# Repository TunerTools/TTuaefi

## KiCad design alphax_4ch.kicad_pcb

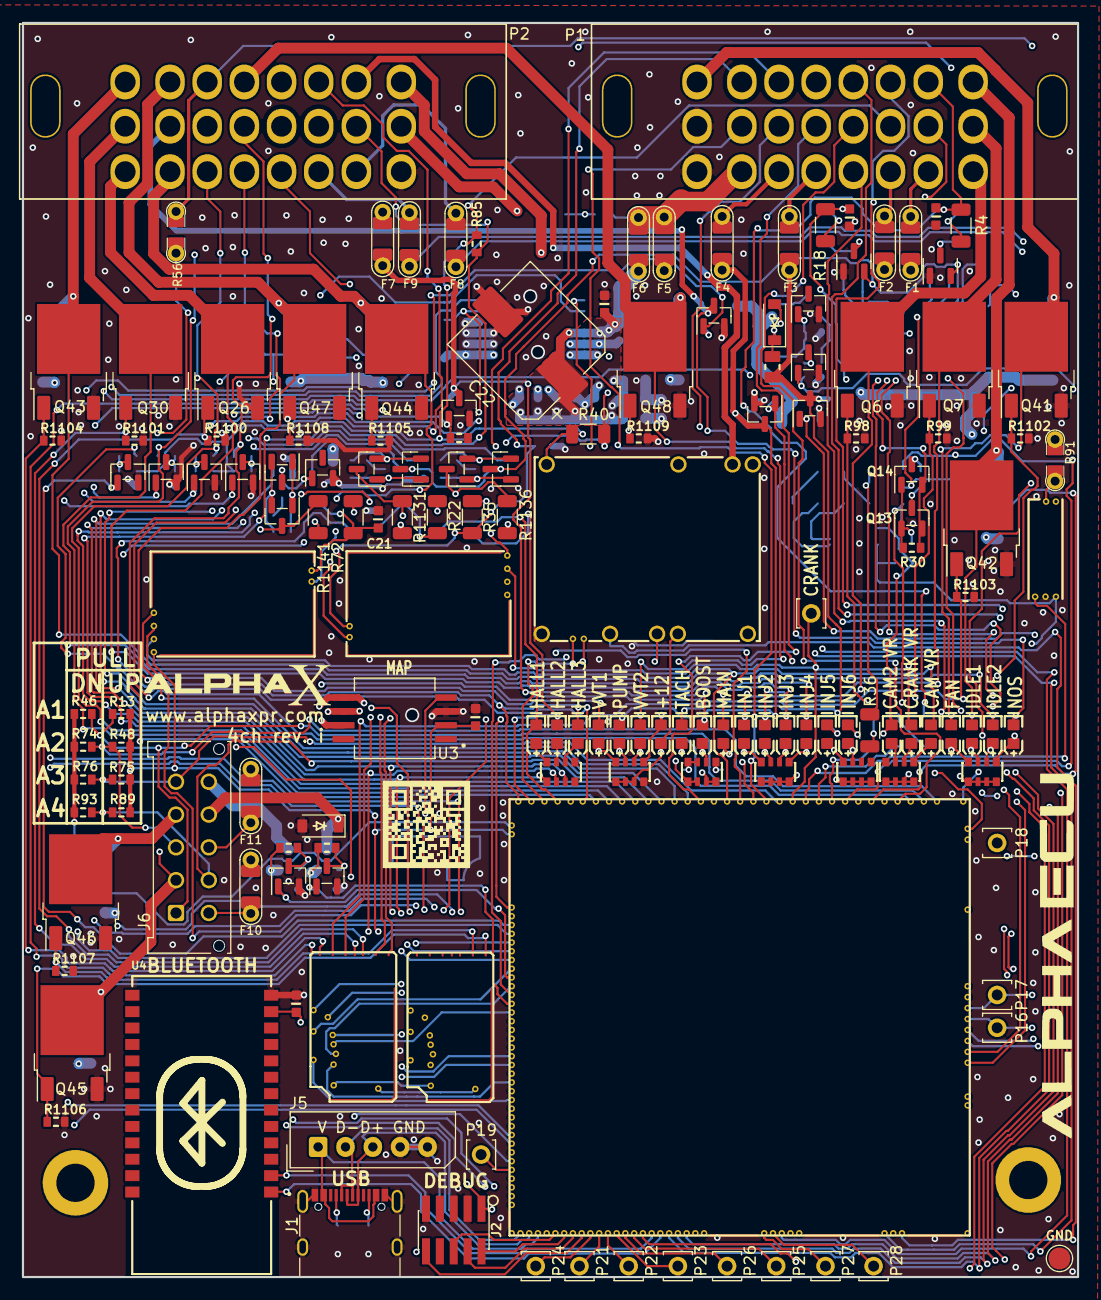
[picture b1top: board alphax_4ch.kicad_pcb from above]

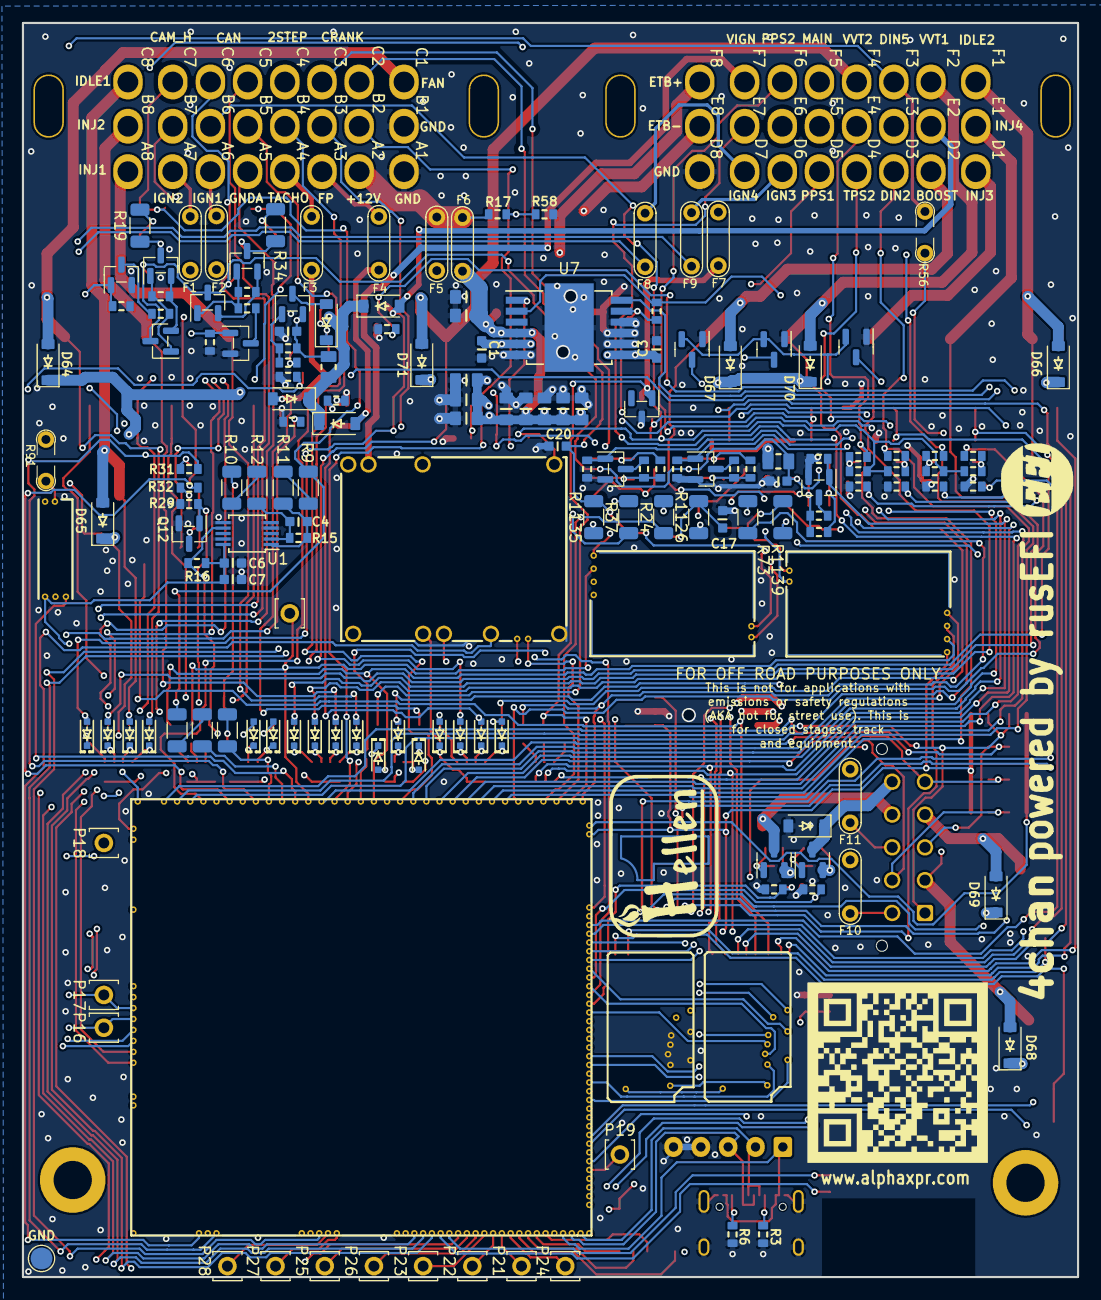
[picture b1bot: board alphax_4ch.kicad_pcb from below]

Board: 4 copper layers, 96.5 x 114.7 mm, 291 parts (134 on the bottom side), 230 nets.

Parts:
C1, C3: 10n; C0603
C2, C5, C6, C18, C19, C55: 100n; C0603
C4: 1n; C0603
C7: 22u; C0603
C8, C9, C17, C20, C21: 1n 250V; C0603
C22: 470uF; CP_Elec_10x10.5
C45, C46, C47, C48, C49, C50, C51, C52, C53, C54: 10u; C0805
D1, D2, D3, D5, D6, D7, D8, D21, D22, D24, D37, D38, D41, D42, D45, D46, D53: 1N4148WS; SOD-323
D4, D10, D33, D34, D35, D36: LED-WHITE-0603; LED-0603
D9, D13, D14, D15, D16, D17, D31, D32, D39, D40, D43, D44, D47, D48, D56, D57: LED-RED-0603; LED-0603
D18, D19, D23, D55, D58: BAT54S; SOT-23
D20: LED-GREEN-0603; LED-0603
D25, D28, D29: PSM712-LF; SOT-23
D26, D27, D49, D50, D51, D52, D64, D65, D66, D67, D68, D69, D70, D71, D72: B5819W; SOD-123
F1, F2, F8, F9, F10, F11: nSMD005; PAD-1206-PAD
F3, F4, F7: nSMD050; PAD-1206-PAD
F5, F6: 12H1500D; PAD-1206-PAD
G1: RUSEFI_LOGO; rusefi_logo
G3: LOGO
G4: LOGO_AlphaECU; alphax_logo_AlphaECU
G5: LOGO_AlphaX; alphax_logo_AlphaX
G6: ALPHAX_QR_CODE; alphax_qr_code
G7: Disclaimer; Off_Road_Disclaimer
J1: USB_C_Receptacle_USB2.0; USB_C_Receptacle_XKB_U262-16XN-4BVC11
J2: Cortex_Debug; PinHeader_2x05_P1.27mm_Vertical_SMD
J3, J4: Conn_01x01; TestPoint_Pad_D2.0mm
J5: Conn_01x05_Male; Molex_SPOX_5267-05A_1x05_P2.50mm_Vertical
J6: 430451012; Molex_Micro-Fit_3.0_43045-1012_2x05_P3.00mm_Vertical
J7, J8: Conn_01x01; MountingHole_4.5mm_Pad
M1: Module-power_12and5V-0.2; power_12and5V
M2, M6: Module-ign8-0.2; ign8
M3, M8: Module-vr-discrete-0.4; vr-discrete
M4: Module-mega-mcu144-0.5; mega-mcu144
M9: Module-knock-0.2; knock
P1: HCCPHPE24BKA90F; 33311-24AW-2
P2: HCCPHPE24BGYB90F; 33311-24AW-2
P4, P16, P17, P18, P19, P21, P22, P23, P24, P25, P26, P27, P28: Pad; PAD-TH
Q1, Q3, Q4, Q8, Q9, Q10, Q11, Q12, Q17, Q20, Q22, Q23, Q24, Q27, Q29, Q31, Q51: AO3400A; SOT-23
Q2, Q16: PJM2319PSA; SOT-23
Q6, Q7, Q26, Q30, Q41, Q42, Q43, Q44, Q45, Q46, Q47, Q48: VND14NV04-E; DPAK
Q13, Q14, Q18, Q19, Q21, Q25, Q28, Q35, Q36, Q49, Q50, Q52, Q53: AO3401A; SOT-23
R1, R2, R5, R26, R50, R51: 4.7k; R0603-4
R3, R6: 5.6k; R0603
R4, R18, R19, R34, R1126, R1131, R1135, R1136, R1139, R1141: 2k; R_1206_3216Metric
R7, R8, R14, R20, R27, R29, R30, R38, R39, R41, R42, R43, R44, R52, R53, R54, R55, R57, R86, R87, R88, R98, R99, R1100, R1101, R1102, R1103, R1104, R1105, R1106, R1107, R1108, R1109, R1110, R1111, R1112, R1113, R1125, R1127, R1128, R1129, R1132, R1137, R1138, R1140: 4.7k; R0603
R9, R10, R11, R12, R21, R22, R23, R24, R35, R36, R37, R47, R72, R73: 4.7k; R_1206_3216Metric
R13, R15, R48, R75, R89: R0603
R16: 10k; R0603
R17: 33k; R0603
R25: 470; R0805
R28, R78, R79, R80: 1.2k; R0603
R31, R32: 2.7k; R0603
R33: 220; R0805
R40: SMD1206B035TF/16; R_1206_3216Metric
R45: 750; R0805
R46, R74, R76, R93: 680k; R0603
R49: 1k; R0603-4
R56, R91: Jumper-Pad-Pad; PAD-0805-PAD
R58: 6.8k; R0603
R81, R82, R83, R84, R85: 3.3k; R0603
U1: MAX9924UAUB+; MSOP-10_3x3mm_P0.5mm
U3: MPXH6400A; MPXH6400A-SSOP8
U4: JDY-33
U7: TLE9201SG; Infineon_PG-DSO-12-11

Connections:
+3.3V: J2.1, M4.N22 (V33), R8.2, U7.2 (VSO)
+3.3VA: C19.2, M2.V10 (V33), M4.N28 (V33_SWITCHABLE), M6.V10 (V33), U4.12 (3V3)
+5V: M1.E4 (V5), M4.N31 (VCC)
+5VA: C2.2, C6.2, C7.2, D27.2 (A), M2.V9 (VCC), M3.E4 (V5_IN), M4.E38 (V5A_SWITCHABLE), M4.W2 (V5A_SWITCHABLE), M6.V9 (VCC), M8.E4 (V5_IN), M9.E1 (V5A), R1.1, R1.2, R1.3, R1.4, R13.2, R16.2, R40.1, R48.2, R50.1, R50.2, R75.2, R89.2, U1.10 (VCC), U3.2 (Vs)
+5VAS: M1.V4 (5VP), P1.14 (B6), Q13.3 (S), Q14.3 (S), R28.2, R30.2, R40.2, R78.2, R79.2, R80.2, R85.2
+12V: D20.1 (A), D22.1 (K), M1.E2 (V12), R2.1, R2.2, R2.3, R2.4, R5.1, R5.2, R5.3, R26.1, R26.2, R26.3, R26.4, R50.3, R50.4, R51.1, R51.2, R51.3, R51.4
+12V_ETB: C22.1, C45.2, C46.2, C47.2, C48.2, C49.2, C50.2, C51.2, C52.2, C53.2, C54.2, C55.2, F6.2, U7.4 (VS)
+12V_RAW: D49.1 (K), D52.1 (K), D64.1 (K), D65.1 (K), D66.1 (K), D67.1 (K), D68.1 (K), D69.1 (K), D70.1 (K), D71.1 (K), D72.1 (K), F5.2, M1.V1 (V12_PERM), M1.V3 (V12_RAW), Q2.2 (S), Q16.2 (S), R7.2, R20.2, R25.2, R33.2
/2STEP_PULLUP: M4.E23 (OUT_IO7), Q31.1 (G), R57.1
/A2: F5.1, F6.1, P1.2 (A2), R17.1
/A3: F4.1, P1.3 (A3)
/A4: F3.1, P1.4 (A4)
/A6: F2.1, P1.6 (A6)
/A7: F1.1, P1.7 (A7)
/AIN1: J6.1, M4.S32 (IN_TPS2), R13.1, R46.2
/AIN2: J6.3, M4.S33 (IN_PPS2), R48.1, R74.2
/AIN3: J6.5, M4.S21 (IN_MAP1), R75.1, R76.2
/AIN4: J6.7, M4.S11 (IN_AUX3), R89.1, R93.2
/BOOST: M2.S1 (OUT_IGN8), Q44.1 (IN), R1105.1
/CAM2_VR: D4.2 (K), M4.E36 (IO7), R16.1, U1.7 (COUT)
/CAM_PULLUP: M4.N20 (IO4), Q29.1 (G), R55.2
/CAM_VR_PULLUP: M4.E11 (OUT_IO9), Q51.1 (G), R49.3, R1137.1
/CAN+: M4.W12 (CANH), P1.21 (C5)
/CAN-: M4.W13 (CANL), P1.22 (C6)
/CRANK_N_PULLUP: M4.E7 (OUT_IO5), Q1.1 (G), R41.2, R49.2
/CRANK_P_PULLUP: M4.E12 (OUT_IO2), Q3.1 (G), R49.1, R1125.2
/D2_PULLDOWN: M4.E20 (OUT_IO13), Q8.1 (G), R88.1
/D3_PULLDOWN: M4.E22 (OUT_IO8), Q9.1 (G), R87.1
/D4_PULLDOWN: M4.E33 (OUT_INJ7), Q22.1 (G), R86.1
/D5_PULLDOWN: M4.E34 (OUT_INJ8), Q23.1 (G), R27.1
/D6: F9.1, P2.6 (D6)
/D7: F8.1, P2.7 (D7)
/ETB_DIR: M4.N16 (IO1), U7.1 (DIR)
/ETB_DIS: M4.N19 (IO2), R8.1, U7.11 (DIS)
/ETB_PWM: M4.E17 (OUT_PWM2), U7.12 (PWM)
/F3: P2.19 (F3), R56.2, R91.2
/F5: F7.1, P2.21 (F5)
/FAN_RELAY: M2.S4 (OUT_IGN5), Q41.1 (IN), R1102.1
/HALL1: D34.2 (K), M4.S4 (IN_D1), R24.1
/HALL2: D35.2 (K), M4.S2 (IN_D3), R37.1
/HALL3: D36.2 (K), M4.S1 (IN_D4), R73.1
/HALL_OPT_PU/+12V_LIM: C18.2, D18.2 (K), D19.2 (K), D23.2 (K), D28.1, D55.2 (K), D58.2 (K), Q18.2 (D), Q25.2 (D), Q35.2 (D), Q49.2 (D), Q52.2 (D), R25.1
/HS/IN1: M4.E25 (OUT_PWM7), Q4.1 (G), R14.1
/HS/IN2: M4.E28 (OUT_PWM8), Q17.1 (G), R38.1
/IDLE1: M2.S3 (OUT_IGN6), Q42.1 (IN), R1103.1
/IDLE2: M2.S2 (OUT_IGN7), Q43.1 (IN), R1104.1
/INJ1: M2.S8 (OUT_IGN1), Q6.1 (IN), R98.1
/INJ2: M2.S7 (OUT_IGN2), Q7.1 (IN), R99.1
/INJ3: M2.S6 (OUT_IGN3), Q26.1 (IN), R1100.1
/INJ4: M2.S5 (OUT_IGN4), Q30.1 (IN), R1101.1
/INJ5: M6.S8 (OUT_IGN1), Q45.1 (IN), R1106.1
/INJ6: M6.S7 (OUT_IGN2), Q46.1 (IN), R1107.1
/IN_2STEP: M4.S25 (IN_VSS), R47.1
/IN_2STEP_CAM2_VR-: C8.2, P1.20 (C4), R10.2, R18.2, R36.2
/IN_AFR: M4.S15 (IN_O2S2), P1.12 (B4)
/IN_CAM_HALL: M4.S24 (IN_CAM), R23.1
/IN_CAM_HALL_CAM2_VR+: C9.2, P1.23 (C7), R4.2, R9.2, R21.2
/IN_CAM_VR: D33.2 (K), M3.E3 (OUT), M4.S17 (IN_RES1)
/IN_CAM_VR+: C21.2, M3.W2 (VR+), P2.14 (E6), R72.2, R1139.2
/IN_CAM_VR-: M3.W1 (VR-), P2.13 (E5)
/IN_CLT: M4.S28 (IN_CLT), P1.15 (B7), R32.2
/IN_CRANK: D10.2 (K), M4.S22 (IN_CRANK), M8.E3 (OUT), P4.1
/IN_CRANK+: C17.2, M8.W2 (VR+), P1.19 (C3), R22.2, R1126.2
/IN_CRANK-: C20.2, M8.W1 (VR-), P1.18 (C2), R35.2, R1135.2
/IN_D2: M4.S9 (IN_SENS1), P2.3 (D3), R81.1
/IN_D3: M4.S8 (IN_SENS2), P2.11 (E3), R82.1
/IN_D4: M4.S7 (IN_SENS3), P2.12 (E4), R83.1
/IN_D5: M4.S6 (IN_SENS4), R56.1, R84.1
/IN_FLEX: M4.S10 (IN_AUX4), P2.15 (E7), R85.1
/IN_IAT: M4.S26 (IN_IAT), P1.11 (B3), R31.2
/IN_KNOCK: M4.S23 (IN_KNOCK), M9.E3 (OUT_KNOCK)
/IN_KNOCK_RAW: M9.W1 (IN_KNOCK), R91.1
/IN_MAP: M4.S20 (IN_MAP2), P1.10 (B2)
/IN_MAP2: M4.S19 (IN_MAP3), U3.4 (Vout)
/IN_PPS1: M4.S31 (IN_PPS), P2.5 (D5)
/IN_PPS2: M4.S12 (IN_AUX2), P2.22 (F6)
/IN_TPS1: M4.S30 (IN_TPS), P1.13 (B5)
/IN_TPS2: M4.S13 (IN_AUX1), P2.4 (D4)
/IN_VIGN: M1.V2 (IN_VIGN), P2.23 (F7)
/IN_VMAIN: M4.S27 (IN_AT1), R17.2, R58.2
/MAIN: M4.E10 (OUT_IO10), Q10.1 (G), R1113.1
/MCU/NRESET: J2.10, M4.N9 (nReset)
/MCU/SWCLK: J2.4, M4.N8 (SWCLK)
/MCU/SWDIO: J2.2, M4.N7 (SWDIO)
/MCU/SWO: J2.6, M4.N6 (SWO)
/MCU/UART_RX: M4.N18 (UART2_RX), U4.1 (TXD)
/MCU/UART_TX: M4.N17 (UART2_TX), U4.2 (RXD)
/MCU/USB+: J1.A6 (D+), J1.B6 (D+), J5.3, M4.N3 (USBP)
/MCU/USB-: J1.A7 (D-), J1.B7 (D-), J5.2, M4.N2 (USBM)
/MCU/VBUS: J1.A4 (VBUS), J1.A9 (VBUS), J1.B4 (VBUS), J1.B9 (VBUS), J5.1, M4.N4 (VBUS)
/MCU_BOOST: M2.V1 (IGN8), M4.E16 (OUT_PWM3)
/MCU_FAN_RELAY: M2.V4 (IGN5), M4.E24 (OUT_IO11)
/MCU_IDLE1: M2.V3 (IGN6), M4.E27 (OUT_PWM1)
/MCU_IDLE2: M2.V2 (IGN7), M4.E14 (OUT_PWM5)
/MCU_INJ1: M2.V8 (IGN1), M4.E19 (OUT_INJ1)
/MCU_INJ2: M2.V7 (IGN2), M4.E18 (OUT_INJ2)
/MCU_INJ3: M2.V6 (IGN3), M4.E29 (OUT_INJ3)
/MCU_INJ4: M2.V5 (IGN4), M4.E30 (OUT_INJ4)
/MCU_INJ5: M4.E31 (OUT_INJ5), M6.V8 (IGN1)
/MCU_INJ6: M4.E32 (OUT_INJ6), M6.V7 (IGN2)
/NOS: M4.E9 (OUT_IO6), Q27.1 (G), R1110.1
/OUT_BOOST: D37.2 (A), D43.2 (K), D67.2 (A), P2.2 (D2), Q44.2 (D)
/OUT_ETB+: C3.2, P2.24 (F8), U7.7 (OUT2)
/OUT_ETB-: C1.2, P2.16 (E8), U7.5 (OUT1)
/OUT_FAN_RELAY: D5.2 (A), D13.2 (K), D64.2 (A), P1.17 (C1), Q41.2 (D)
/OUT_HS1: D50.1 (K), J6.9, Q2.3 (D)
/OUT_HS2: D51.1 (K), J6.10, Q16.3 (D)
/OUT_IDLE1: D6.2 (A), D14.2 (K), D65.2 (A), P1.24 (C8), Q42.2 (D)
/OUT_IDLE2: D2.2 (A), D31.2 (K), D66.2 (A), P2.17 (F1), Q43.2 (D)
/OUT_IGN1: F2.2, M4.W11 (IGN1)
/OUT_IGN2: F1.2, M4.W10 (IGN2)
/OUT_IGN3: F9.2, M4.W9 (IGN3)
/OUT_IGN4: F8.2, M4.W8 (IGN4)
/OUT_IGN5: F10.2, M4.W7 (IGN5), P16.1
/OUT_IGN6: F11.2, M4.W6 (IGN6), P17.1
/OUT_INJ1: D7.2 (A), D15.2 (K), P1.8 (A8), Q6.2 (D)
/OUT_INJ2: D8.2 (A), D16.2 (K), P1.16 (B8), Q7.2 (D)
/OUT_INJ3: D41.2 (A), D47.2 (K), P2.1 (D1), Q26.2 (D)
/OUT_INJ4: D42.2 (A), D48.2 (K), P2.9 (E1), Q30.2 (D)
/OUT_INJ5: D24.2 (A), D56.2 (K), D68.2 (A), J6.2, Q45.2 (D)
/OUT_INJ6: D53.2 (A), D57.2 (K), D69.2 (A), J6.4, Q46.2 (D)
/OUT_MAIN: D29.1, D44.2 (K), F7.2, Q10.2 (D)
/OUT_NOS: D3.2 (A), D32.2 (K), D72.2 (A), P2.10 (E2), Q27.2 (D)
/OUT_PUMP_RELAY: D17.2 (K), D21.2 (A), D52.2 (A), F4.2, Q24.2 (D)
/OUT_TACH: D9.2 (K), D49.2 (A), F3.2, Q11.2 (D), R45.2
/OUT_VVT1: D39.2 (K), D45.2 (A), D70.2 (A), P2.18 (F2), Q47.2 (D)
/OUT_VVT2: D40.2 (K), D46.2 (A), D71.2 (A), P2.20 (F4), Q48.2 (D)
/PUMP_RELAY: M4.E13 (OUT_IO12), Q24.1 (G), R1111.1
/PWR_EN: M1.E5 (EN_5VP), M4.N29 (OUT_PWR_EN)
/TACH: M4.N21 (IO3), Q11.1 (G), R1112.1
/TACH_PULLUP: M4.E8 (OUT_IO1), Q20.1 (G), R44.2
/TEMP_PULLUP: M4.E21 (OUT_IO4), Q12.1 (G), R29.1
/THRESHOLD_VR_CM: M3.E1 (Thresh_IN), M4.E15 (OUT_PWM4)
/THRESHOLD_VR_CR: M4.E26 (OUT_PWM6), M8.E1 (Thresh_IN)
/TLS115_PG: M1.E6 (PG_5VP), M4.S3 (IN_D2)
/VIGN: M1.E3 (VIGN), M4.N26 (IN_VIGN)
/VREF: M4.S35 (VREF1), M9.W2 (VREF)
/VR_ANALOG_CM: M3.E2 (OUT_A), M4.S14 (IN_RES2)
/VR_ANALOG_CR: M4.S18 (IN_RES3), M8.E2 (OUT_A)
/VVT1: M4.W5 (IGN7), Q47.1 (IN), R1108.1
/VVT2: M4.W4 (IGN8), Q48.1 (IN), R1109.1
GND: C1.1, C2.1, C3.1, C5.1, C6.1, C7.1, C8.1, C9.1, C17.1, C18.1, C19.1, C20.1, C21.1, C22.2, C45.1, C46.1, C47.1, C48.1, C49.1, C50.1, C51.1, C52.1, C53.1, C54.1, C55.1, D18.1 (A), D19.1 (A), D23.1 (A), D25.3, D28.3, D29.2, D50.2 (A), D51.2 (A), D55.1 (A), D58.1 (A), J1.A1 (GND), J1.A12 (GND), J1.B1 (GND), J1.B12 (GND), J1.S1 (SHIELD), J2.3, J2.5, J2.9, J3.1, J4.1, J5.4, J5.5, M1.S1 (GND), M2.G (GND), M3.G (GND), M4.G (GND), M6.G (GND), M6.V1 (IGN8), M6.V2 (IGN7), M6.V3 (IGN6), M6.V4 (IGN5), M6.V5 (IGN4), M6.V6 (IGN3), M8.G (GND), M9.E2 (GND), P1.1 (A1), P1.9 (B1), P2.8 (D8), Q1.3 (S), Q3.3 (S), Q4.3 (S), Q6.3 (S), Q7.3 (S), Q8.3 (S), Q9.3 (S), Q10.3 (S), Q11.3 (S), Q12.3 (S), Q17.3 (S), Q20.3 (S), Q22.3 (S), Q23.3 (S), Q24.3 (S), Q26.3 (S), Q27.3 (S), Q29.3 (S), Q30.3 (S), Q31.3 (S), Q41.3 (S), Q42.3 (S), Q43.3 (S), Q44.3 (S), Q45.3 (S), Q46.3 (S), Q47.3 (S), Q48.3 (S), Q51.3 (S), R3.1, R5.4, R6.1, R14.2, R27.2, R29.2, R38.2, R41.1, R44.1, R55.1, R57.2, R58.1, R86.2, R87.2, R88.2, R98.2, R99.2, R1100.2, R1101.2, R1102.2, R1103.2, R1104.2, R1105.2, R1106.2, R1107.2, R1108.2, R1109.2, R1110.2, R1111.2, R1112.2, R1113.2, R1125.1, R1137.2, U1.4 (BIAS), U1.5 (GND), U1.6 (ZERO_EN), U1.9 (INT_THRS), U3.3 (GND), U4.13 (GND), U7.6 (GND), U7.8 (SI), U7.9 (CSN), U7.10 (SCK), U7.13 (GND)
GNDA: M4.E39 (GNDA), M4.W1 (GNDA), P1.5 (A5), R46.1, R74.1, R76.1, R93.1
unnamed: D1.2 (A), R50.7, R50.8
unnamed: D1.1 (K), D9.1 (A)
unnamed: D2.1 (K), D31.1 (A), R2.6
unnamed: D3.1 (K), D32.1 (A), R2.5
unnamed: D4.1 (A), R1.7
unnamed: D10.1 (A), R1.6
unnamed: D5.1 (K), D13.1 (A), R2.8
unnamed: D6.1 (K), D14.1 (A), R2.7
unnamed: D7.1 (K), D15.1 (A), R51.8
unnamed: D8.1 (K), D16.1 (A), R51.7
unnamed: D17.1 (A), D21.1 (K), R5.7
unnamed: D18.3 (COM), Q36.2 (D), R1131.1
unnamed: D19.3 (COM), Q50.2 (D), R1136.1
unnamed: D20.2 (K), D22.2 (A), R5.5
unnamed: D23.3 (COM), Q53.2 (D), R1141.1
unnamed: D24.1 (K), D56.1 (A), R26.8
unnamed: D26.2 (A), Q21.2 (D)
unnamed: D26.1 (K), D27.1 (K), R45.1
unnamed: D33.1 (A), R1.5
unnamed: D34.1 (A), R49.8
unnamed: D35.1 (A), R49.7
unnamed: D36.1 (A), R49.6
unnamed: D37.1 (K), D43.1 (A), R50.6
unnamed: D38.2 (A), R50.5
unnamed: D38.1 (K), D44.1 (A)
unnamed: D39.1 (A), D45.1 (K), R5.8
unnamed: D40.1 (A), D46.1 (K), R5.6
unnamed: D41.1 (K), D47.1 (A), R51.6
unnamed: D42.1 (K), D48.1 (A), R51.5
unnamed: D53.1 (K), D57.1 (A), R26.7
unnamed: D55.3 (COM), Q19.2 (D), R19.1
unnamed: D58.3 (COM), Q28.2 (D), R34.1
unnamed: J1.A5 (CC1), R3.2
unnamed: J1.B5 (CC2), R6.2
unnamed: F10.1, J6.6
unnamed: F11.1, J6.8
unnamed: M4.N14 (I2C_SCL), P26.1
unnamed: M4.N15 (I2C_SDA), P25.1
unnamed: M4.S29 (IN_AT2), P18.1
unnamed: M4.E6 (OUT_IO3), P19.1
unnamed: M4.N10 (SPI3_CS), P24.1
unnamed: M4.N12 (SPI3_MISO), P22.1
unnamed: M4.N13 (SPI3_MOSI), P23.1
unnamed: M4.N11 (SPI3_SCK), P21.1
unnamed: M4.N24 (UART8_RX), P27.1
unnamed: M4.N25 (UART8_TX), P28.1
unnamed: Q1.2 (D), R1128.1
unnamed: Q2.1 (G), Q4.2 (D), R7.1
unnamed: Q3.2 (D), R1132.1
unnamed: Q8.2 (D), R28.1, R81.2
unnamed: Q9.2 (D), R78.1, R82.2
unnamed: Q12.2 (D), Q13.1 (G), Q14.1 (G), R30.1
unnamed: Q13.2 (D), R32.1
unnamed: Q14.2 (D), R31.1
unnamed: Q16.1 (G), Q17.2 (D), R20.1
unnamed: Q18.1 (G), Q19.1 (G), R39.1, R52.2
unnamed: Q18.3 (S), Q19.3 (S), R39.2
unnamed: Q20.2 (D), R43.1
unnamed: Q21.1 (G), R42.1, R43.2
unnamed: C5.2, D25.1, Q21.3 (S), R33.1, R42.2
unnamed: Q22.2 (D), R79.1, R83.2
unnamed: Q23.2 (D), R80.1, R84.2
unnamed: Q25.1 (G), Q28.1 (G), R53.1, R54.2
unnamed: Q25.3 (S), Q28.3 (S), R53.2
unnamed: Q29.2 (D), R52.1
unnamed: Q31.2 (D), R54.1
unnamed: Q35.1 (G), Q36.1 (G), R1129.1, R1132.2
unnamed: Q35.3 (S), Q36.3 (S), R1129.2
unnamed: Q49.1 (G), Q50.1 (G), R1127.1, R1128.2
unnamed: Q49.3 (S), Q50.3 (S), R1127.2
unnamed: Q51.2 (D), R1138.1
unnamed: Q52.1 (G), Q53.1 (G), R1138.2, R1140.1
unnamed: Q52.3 (S), Q53.3 (S), R1140.2
unnamed: R10.1, R12.2
unnamed: R9.1, R11.2
unnamed: R18.1, R34.2
unnamed: R4.1, R19.2
unnamed: R21.1, R23.2
unnamed: R22.1, R24.2
unnamed: R35.1, R37.2
unnamed: R36.1, R47.2
unnamed: R72.1, R73.2
unnamed: R1126.1, R1131.2
unnamed: R1135.1, R1136.2
unnamed: R1139.1, R1141.2
unnamed: C4.2, R11.1, R15.2, U1.1 (IN+)
unnamed: C4.1, R12.1, R15.1, U1.2 (IN-)

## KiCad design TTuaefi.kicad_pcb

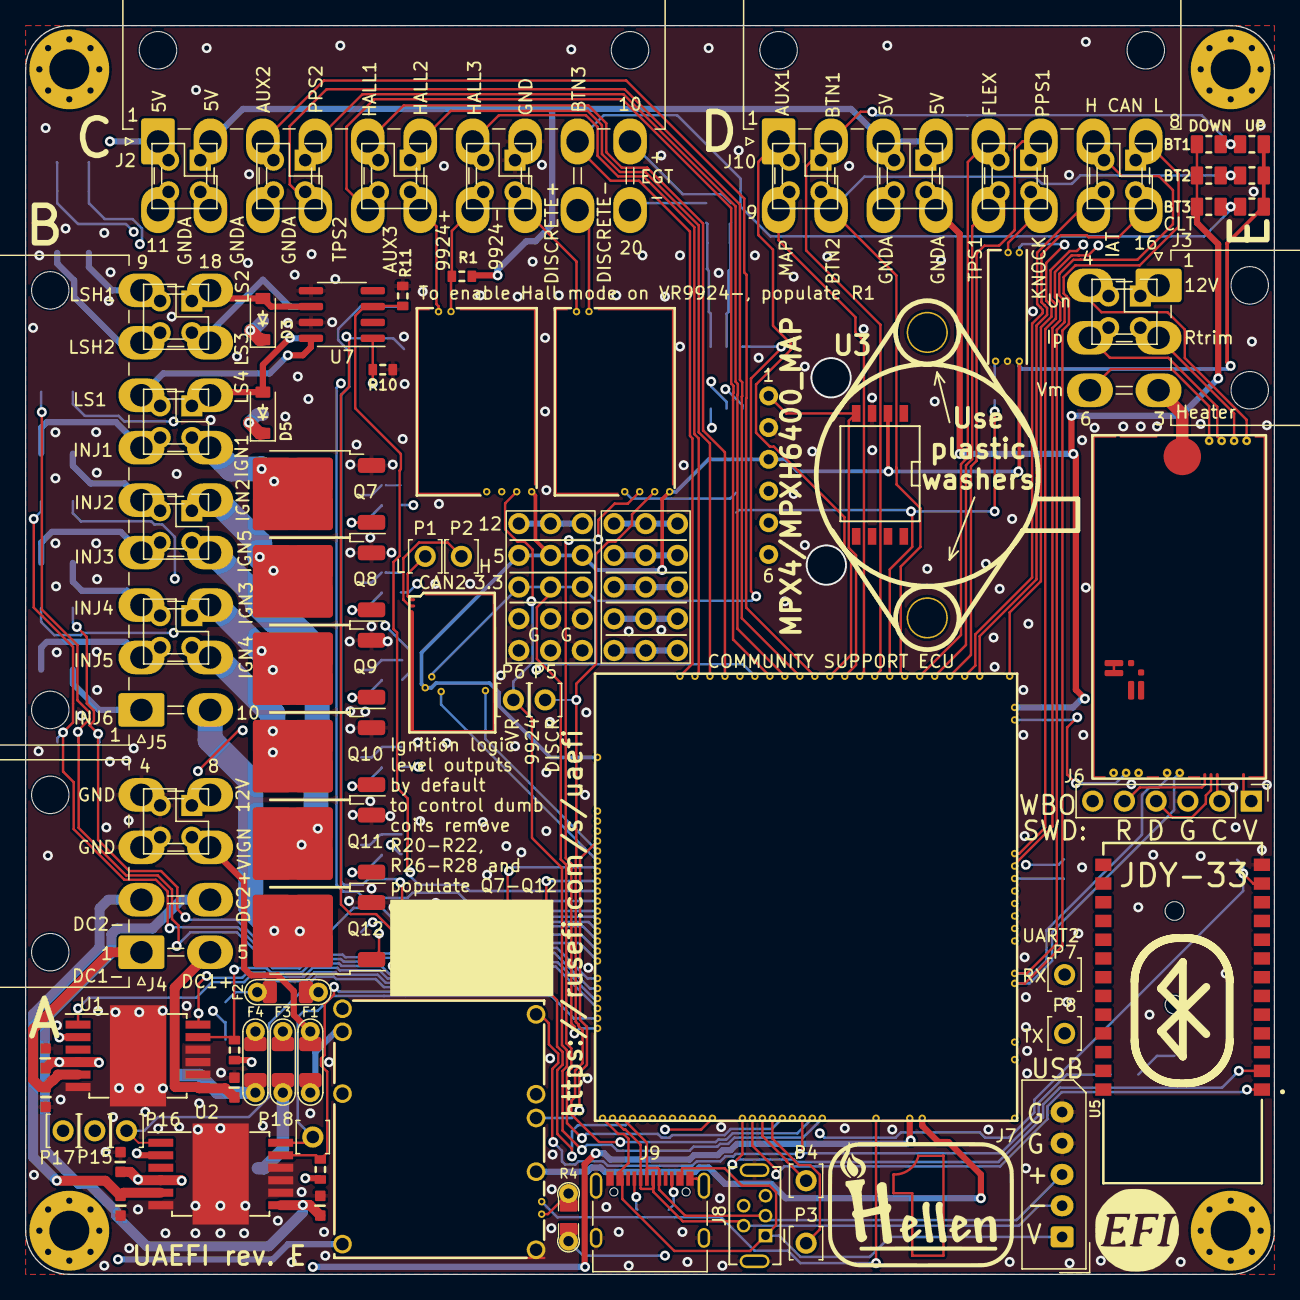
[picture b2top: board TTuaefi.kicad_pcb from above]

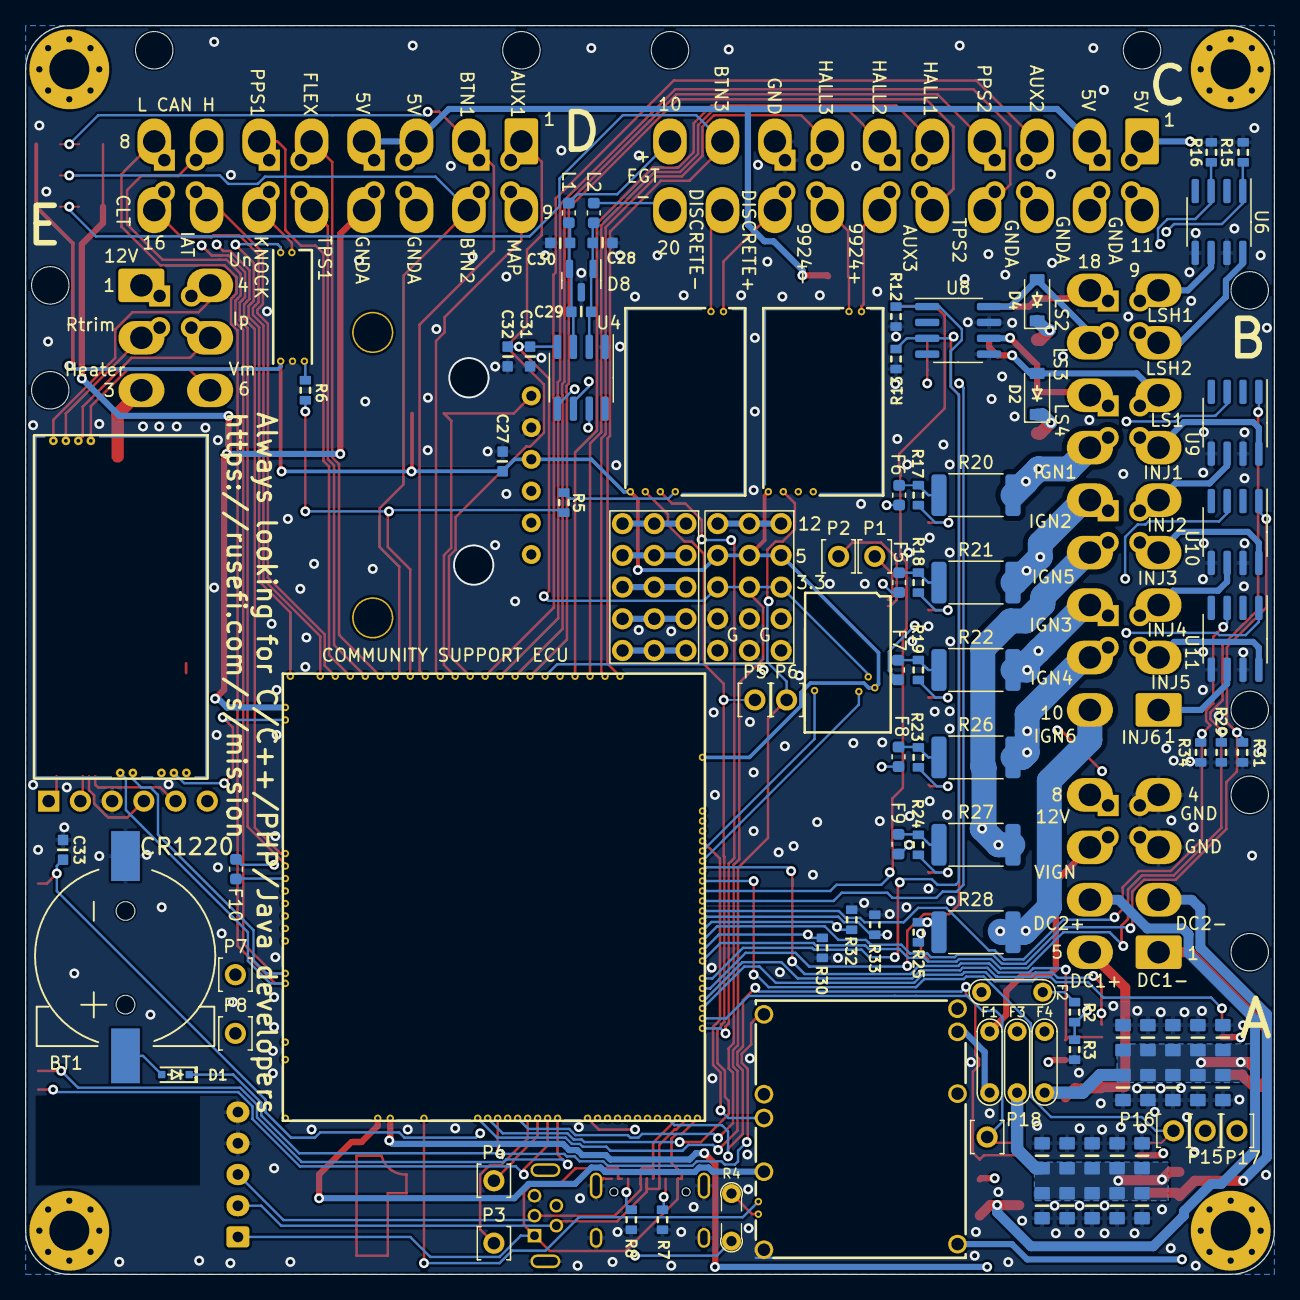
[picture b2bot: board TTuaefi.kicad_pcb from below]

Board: 4 copper layers, 100.0 x 100.0 mm, 159 parts (74 on the bottom side), 145 nets.

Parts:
BT1: CR1220; CR1220-2
C1, C2, C3, C4, C5, C6, C7, C8, C9, C10, C14, C15, C16, C17, C18, C19, C20, C21, C22, C23: 10u; C0805
C11, C24, C27, C29, C31, C33: 100n; C0603
C12, C13, C25, C26, C28, C30: 10n; C0603
C32: 1u; C0603
D1: 1N4148WS; SOD-323
D2, D3, D4, D5: B5819W; SOD-123
D8: NUP2105L; SOT-23
F1, F2, F3, F4: 12H1500D; PAD-1206-PAD
F5, F6, F7, F8, F9, F10: 50mA; Fuse_0603_1608Metric
G1: RUSEFI_LOGO; rusefi_logo
G2: LOGO
G3, G4: PROTO_AREA
H1, H2, H3, H4: M3; MountingHole_3.2mm_M3_Pad_Via
J1, J11, J12, J13, J14, J15, J16, J17, J18, J19, J20, J21, J22, J24: Conn_02x02_Odd_Even; PinSocket_2x02_P2.54mm_Vertical
J2: 5569-20A2; Molex_Mini-Fit_Jr_5569-20A2_2x10_P4.20mm_Horizontal
J3: 5569-06A2; Molex_Mini-Fit_Jr_5569-06A2_2x03_P4.20mm_Horizontal
J4: 5569-08A2; Molex_Mini-Fit_Jr_5569-08A2_2x04_P4.20mm_Horizontal
J5: 5569-18A2; Molex_Mini-Fit_Jr_5569-18A2_2x09_P4.20mm_Horizontal
J6: Conn_01x06; PinHeader_1x06_P2.54mm_Vertical
J7: Conn_01x05_Male; Molex_SPOX_5267-05A_1x05_P2.50mm_Vertical
J8: USB_B_Mini; USB-MINI-B-VERTICAL
J9: USB_C
J10: 5569-16A2; Molex_Mini-Fit_Jr_5569-16A2_2x08_P4.20mm_Horizontal
L1, L2: 470R@100MHz; L_0603_1608Metric
M1: Module-power_12and5V-0.3; power_12and5V
M2: Module-knock-0.2; knock
M3: Module-vr-discrete-0.5; vr-discrete
M4: Module-vr-max9924-0.1; vr-max9924
M5: Module-wbo-0.5; wbo
M6: Module:mega-mcu100/0.3; mega-mcu100
M7: Module-can-0.1; can
P1, P2, P3, P4, P5, P6, P7, P8, P15, P16, P17, P18: Pad; PAD-TH
Q7, Q8, Q9, Q10, Q11, Q12: ISL9V3040D3ST; TO-252-2
R1, R9, R10, R11, R12, R13, R14, R15, R16, R29, R30, R31, R32, R33, R34: 4.7k; R0603
R2: 33k; R0603
R3: 6.8k; R0603
R4: Jumper-Pad-Pad; PAD-0805-PAD
R5, R6: 0; R0603
R7, R8: 5.6k; R0603
R17, R18, R19, R23, R24, R25: 22; R0603
R20, R21, R22, R26, R27, R28: 0; R_2512_6332Metric
R35, R36, R37: 10k; R0805
R38, R39, R40: DNP; R0805
U1, U2: TLE9201SG; Infineon_PG-DSO-12-11
U3: MPX4/MPXH6400_MAP; MPX-4_MAP
U4: MAX31855KASA; SOIC-8_3.9x4.9mm_P1.27mm
U5: JDY-33
U6, U7, U8, U9, U10, U11: VNLD5160TR-E; SOIC-8_3.9x4.9mm_P1.27mm

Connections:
+3.3V: M6.N21 (V33), R9.2, R14.2, U1.2 (VSO), U2.2 (VSO)
+3.3VA: C31.2, C32.2, C33.2, G3.3, G3.8, G3.13, M6.N15 (V33_SWITCHABLE), M7.V2 (CAN_VIO), U4.4 (V_CC), U5.12 (3V3)
+5V: M1.E4 (V5), M6.N22 (VCC)
+5VA: C27.2, G3.4, G3.9, G3.14, M2.E1 (V5A), M3.E4 (V5_IN), M4.E4 (V5_IN), M5.W1 (V5_IN), M6.E1 (V5A_SWITCHABLE), M6.W2 (V5A_SWITCHABLE), M7.V1 (V5), R38.2, R39.2, R40.2, U3.3 (VCC)
+5VP: J2.1, J2.2, J10.3, J10.4, J12.1, J12.2, J14.1, J14.2, M1.V4 (5VP), R1.1
+12V: F2.1, F3.1, F4.1, J4.8, J22.1, R2.2
+12V_RAW: D2.1 (K), D3.1 (K), D4.1 (K), D5.1 (K), F2.2, G3.5, G3.10, G3.15, J3.1, J24.1, M1.V1 (V12_PERM), M1.V3 (V12_RAW)
/12V_KEY: F1.1, J4.7, J22.3
/ADC3: M6.S15 (IN_KNOCK_(PA2)), R5.2, R6.2
/CAN+: J1.2, J10.7, M5.W4 (CANH), M6.W11 (CANH)
/CAN-: J1.1, J10.8, M5.W3 (CANL), M6.W12 (CANL)
/DC1_DIR: M6.E21 (OUT_PWM4_(PC8)), P15.1, U1.1 (DIR)
/DC1_DIS: M6.E8 (SPI2_MISO_(PB14)), R9.1, U1.11 (DIS)
/DC1_PWM: M6.E20 (OUT_PWM3_(PC7)), P17.1, U1.12 (PWM)
/DC2_DIR: M6.E9 (SPI2_MOSI_(PB15)), P16.1, U2.1 (DIR)
/DC2_DIS: M6.N4 (USBID_(PA10)), R14.1, U2.11 (DIS)
/DC2_PWM: M6.E22 (OUT_PWM5_(PC9)), P18.1, U2.12 (PWM)
/DC Driver 1/PWR: C1.2, C2.2, C3.2, C4.2, C5.2, C6.2, C7.2, C8.2, C9.2, C10.2, C11.2, F4.2, U1.4 (VS)
/DC Driver 2/PWR: C14.2, C15.2, C16.2, C17.2, C18.2, C19.2, C20.2, C21.2, C22.2, C23.2, C24.2, F3.2, U2.4 (VS)
/EGT+: J2.10, L1.1
/EGT-: J2.20, L2.1
/EGT/SPI_CS: M6.N9 (SPI3_CS_(PA15)), U4.6 (~CS)
/IGN1: F6.2, M6.W10 (IGN1_(PC13))
/IGN2: F5.2, M6.W9 (IGN2_(PE5))
/IGN3: F7.2, M6.W8 (IGN3_(PE4))
/IGN4: F8.2, M6.W7 (IGN4_(PE3))
/IGN5: F9.2, M6.W6 (IGN5_(PE2))
/IGN6: F10.2, M6.W5 (IGN6_(PB8))
/INJ1: M6.E17 (OUT_INJ1_(PD3)), R29.2, U9.1 (IN1)
/INJ2: M6.E16 (OUT_INJ2_(PA9)), R30.2, U9.3 (IN2)
/INJ3: M6.E15 (OUT_INJ3_(PD11)), R31.2, U10.1 (IN1)
/INJ4: M6.E14 (OUT_INJ4_(PD10)), R32.2, U10.3 (IN2)
/INJ5: M6.E13 (OUT_INJ5_(PD2)), R33.2, U11.1 (IN1)
/INJ6: M6.E12 (OUT_INJ6_(PA8)), R34.2, U11.3 (IN2)
/INTERNAL_MAP: M6.S12 (IN_MAP2_(PC1)), U3.1 (VOUT)
/IN_AUX1: J10.1, J13.2, M6.S11 (IN_O2S_/_CAN_WAKEUP_(PA0))
/IN_AUX2: J2.3, J15.2, M6.S10 (IN_O2S2_(PA1))
/IN_AUX3: J2.15, J16.4, M6.S7 (IN_AUX3_(PA7))
/IN_BUTTON1: J10.2, J13.1, M6.S14 (IN_CRANK_(PB1)), R35.2, R38.1
/IN_BUTTON2: J10.10, J13.3, M6.S16 (IN_CAM_(PA6)), R36.2, R39.1
/IN_BUTTON3: J2.9, M6.S1 (IN_D4_(PE15)), R37.2, R40.1
/IN_CLT: J1.3, J10.16, M6.S21 (IN_CLT_(PC2))
/IN_FLEX: J10.5, J11.2, M6.S17 (IN_VSS_(PE11))
/IN_HALL1: J2.5, J16.2, M6.S4 (IN_D1_(PE12))
/IN_HALL2: J2.6, J16.1, M6.S3 (IN_D2_(PE13))
/IN_HALL3: J2.7, J17.2, M6.S2 (IN_D3_(PE14))
/IN_IAT: J1.4, J10.15, M6.S20 (IN_IAT_(PC3))
/IN_KNOCK: M2.E3 (OUT_KNOCK), R6.1
/IN_KNOCK_RAW: J10.14, J11.3, M2.W1 (IN_KNOCK)
/IN_MAP: J10.9, J13.4, M6.S13 (IN_MAP1_(PC0))
/IN_PPS1: J10.6, J11.1, M6.S19 (IN_PPS_(PA3))
/IN_PPS2: J2.4, J15.1, M6.S8 (IN_AUX2_(PC4/PE9))
/IN_TPS1: J10.13, J11.4, M6.S18 (IN_TPS_(PA4))
/IN_TPS2: J2.14, J15.3, M6.S9 (IN_AUX1_(PB0))
/IN_VIGN: F1.2, M1.V2 (IN_VIGN)
/IN_VMAIN: M6.S6 (IN_AUX4_(PC5)), R2.1, R3.2
/LS1: M6.E11 (OUT_INJ7_(PD15)), R10.2, U7.1 (IN1)
/LS2: M6.E10 (OUT_INJ8_(PD12)), R11.2, U7.3 (IN2)
/LS3: M6.E18 (OUT_PWM1_(PD13)), R12.2, U8.1 (IN1)
/LS4: M6.E19 (OUT_PWM2_(PC6)), R13.2, U8.3 (IN2)
/LS_HOT1: M6.W4 (IGN7_(PB9)), R16.1, U6.3 (IN2)
/LS_HOT2: M6.W3 (IGN8_(PE6)), R15.1, U6.1 (IN1)
/MISO3: M6.N11 (SPI3_MISO_(PC11)), U4.7 (SO)
/OUT_DC1+: C13.2, J4.5, U1.7 (OUT2)
/OUT_DC1-: C12.2, J4.1, U1.5 (OUT1)
/OUT_DC2+: C26.2, J4.6, U2.7 (OUT2)
/OUT_DC2-: C25.2, J4.2, U2.5 (OUT1)
/OUT_IGN1: J5.15, J19.3, Q7.2 (C), R20.2
/OUT_IGN2: J5.14, J20.1, Q8.2 (C), R21.2
/OUT_IGN3: J5.12, J21.1, Q9.2 (C), R22.2
/OUT_IGN4: J5.11, J21.3, Q10.2 (C), R26.2
/OUT_IGN5: J5.13, J20.3, Q11.2 (C), R27.2
/OUT_IGN6: J5.10, Q12.2 (C), R28.2
/OUT_INJ1: J5.6, J19.4, U9.8 (D1)
/OUT_INJ2: J5.5, J20.2, U9.6 (D2)
/OUT_INJ3: J5.4, J20.4, U10.8 (D1)
/OUT_INJ4: J5.3, J21.2, U10.6 (D2)
/OUT_INJ5: J5.2, J21.4, U11.8 (D1)
/OUT_INJ6: J5.1, U11.6 (D2)
/OUT_LS1: D2.2 (A), J5.7, J19.2, U7.8 (D1)
/OUT_LS2: D3.2 (A), J5.18, J18.1, U7.6 (D2)
/OUT_LS3: D4.2 (A), J5.17, J18.3, U8.8 (D1)
/OUT_LS4: D5.2 (A), J5.16, J19.1, U8.6 (D2)
/OUT_LS_HOT1: J5.9, J18.2, U6.6 (D2)
/OUT_LS_HOT2: J5.8, J18.4, U6.8 (D1)
/PG_5VP: M6.N12 (SPI3_MOSI_(PC12)), R4.2
/PWR_EN: M1.E5 (EN_5VP), M6.N20 (OUT_PWR_EN_(PE10))
/SCK3: M6.N10 (SPI3_SCK_(PC10)), U4.5 (SCK)
/USB+: J7.3, J8.3 (D+), J9.A6 (D+), J9.B6 (D+), M6.N3 (USBP_(PA12))
/USB-: J7.2, J8.2 (D-), J9.A7 (D-), J9.B7 (D-), M6.N2 (USBM_(PA11))
/VBAT: D1.1 (K), M1.E1 (VBAT), M6.N17 (VBAT)
/VBUS: J7.1, J8.1 (VBUS), J9.A4 (VBUS), J9.A9 (VBUS), J9.B4 (VBUS), J9.B9 (VBUS), M6.N1 (VBUS)
/VIGN: M1.E3 (VIGN), M6.E5 (IN_VIGN_(PA5))
/VREF1: M2.W2 (VREF), M6.S22 (VREF1)
/VR_DISCRETE: M3.E3 (OUT), M6.N18 (UART8_RX_(PE0)), P5.1
/VR_DISCRETE+: J2.18, J17.3, M3.W2 (VR+)
/VR_DISCRETE-: J2.19, M3.W1 (VR-)
/VR_DISCRETE_A: M3.E2 (OUT_A), R5.1
/VR_DISCRETE_THR: M3.E1 (Thresh_IN), M6.E23 (OUT_PWM6_(PD14))
/VR_MAX9924: M4.E3 (OUT), M6.N19 (UART8_TX_(PE1)), P6.1
/VR_MAX9924+: J2.16, J16.3, M4.W2 (VR+)
/VR_MAX9924-: J2.17, J17.4, M4.W1 (VR-), R1.2
/WBO_Heater: J3.3, M5.E5 (LSU_H+)
/WBO_Ip: J3.5, J24.4, M5.E3 (LSU_Ip)
/WBO_Rtrim: J3.2, J24.3, M5.E4 (LSU_Rtrim)
/WBO_Un: J3.4, J24.2, M5.E1 (LSU_Un)
/WBO_Vm: J3.6, M5.E2 (LSU_Vm)
GND: BT1.2 (-), C1.1, C2.1, C3.1, C4.1, C5.1, C6.1, C7.1, C8.1, C9.1, C10.1, C11.1, C12.1, C13.1, C14.1, C15.1, C16.1, C17.1, C18.1, C19.1, C20.1, C21.1, C22.1, C23.1, C24.1, C25.1, C26.1, C27.1, C28.1, C30.1, C31.1, C32.1, C33.1, D8.3 (A), G3.1, G3.2, G3.6, G3.7, G3.11, G3.12, J2.8, J4.3, J4.4, J6.3, J7.4, J7.5, J8.5 (GND), J8.6 (Shield), J9.A1 (GND), J9.A12 (GND), J9.B1 (GND), J9.B12 (GND), J9.S1 (SHIELD), J17.1, J22.2, J22.4, M1.S1 (GND), M2.E2 (GND), M3.G (GND), M4.G (GND), M5.E6 (LSU_H-), M5.G (GND), M6.G (GND), M7.E1 (GND), Q7.3 (E), Q8.3 (E), Q9.3 (E), Q10.3 (E), Q11.3 (E), Q12.3 (E), R3.1, R7.1, R8.1, R10.1, R11.1, R12.1, R13.1, R15.2, R16.2, R29.1, R30.1, R31.1, R32.1, R33.1, R34.1, U1.6 (GND), U1.8 (SI), U1.9 (CSN), U1.10 (SCK), U1.13 (GND), U2.6 (GND), U2.8 (SI), U2.9 (CSN), U2.10 (SCK), U2.13 (GND), U3.2 (GND), U4.1 (GND), U5.13 (GND), U6.5 (S2), U6.7 (S1), U7.5 (S2), U7.7 (S1), U8.5 (S2), U8.7 (S1), U9.5 (S2), U9.7 (S1), U10.5 (S2), U10.7 (S1), U11.5 (S2), U11.7 (S1)
GNDA: J2.11, J2.12, J2.13, J10.11, J10.12, J12.3, J12.4, J14.3, J14.4, J15.4, M6.W1 (GNDA), R35.1, R36.1, R37.1
unnamed: BT1.1 (+), D1.2 (A)
unnamed: F5.1, R18.2, R21.1
unnamed: F6.1, R17.2, R20.1
unnamed: F7.1, R19.2, R22.1
unnamed: F8.1, R23.2, R26.1
unnamed: F9.1, R24.2, R27.1
unnamed: F10.1, R25.2, R28.1
unnamed: G4.1, G4.6, G4.11
unnamed: G4.5, G4.10, G4.15
unnamed: G4.2, G4.7, G4.12
unnamed: G4.3, G4.8, G4.13
unnamed: G4.4, G4.9, G4.14
unnamed: J6.1, M5.W8 (V33_OUT)
unnamed: J6.2, M5.W7 (SWCLK)
unnamed: J6.4, M5.W6 (SWDIO)
unnamed: J6.5, M5.W5 (nReset)
unnamed: J9.A5 (CC1), R7.2
unnamed: J9.B5 (CC2), R8.2
unnamed: M1.E6 (PG_5VP), R4.1
unnamed: M5.J1 (SEL1), M5.J_GND1 (PULL_DOWN1)
unnamed: M6.N14a (LED_GREEN), P4.1
unnamed: M6.N14b (LED_YELLOW), P3.1
unnamed: M6.E6 (SPI2_CS_/_CAN2_RX_(PB12)), M7.V6 (CAN_RX)
unnamed: M6.E7 (SPI2_SCK_/_CAN2_TX_(PB13)), M7.V5 (CAN_TX)
unnamed: M6.N14 (UART2_RX_(PD6)), P7.1, U5.1 (TXD)
unnamed: M6.N13 (UART2_TX_(PD5)), P8.1, U5.2 (RXD)
unnamed: M7.S2 (CANH), P2.1
unnamed: M7.S1 (CANL), P1.1
unnamed: Q7.1 (G), R17.1
unnamed: Q8.1 (G), R18.1
unnamed: Q9.1 (G), R19.1
unnamed: Q10.1 (G), R23.1
unnamed: Q11.1 (G), R24.1
unnamed: Q12.1 (G), R25.1
unnamed: C29.2, C30.2, D8.2 (K), L1.2, U4.3 (T+)
unnamed: C28.2, C29.1, D8.1 (K), L2.2, U4.2 (T-)

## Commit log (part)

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2025-11-15 GHA says update hellen-one
2025-11-16 [skip actions] Auto-generated board v2.1
2025-11-20 GHA says update kicad6-libraries
